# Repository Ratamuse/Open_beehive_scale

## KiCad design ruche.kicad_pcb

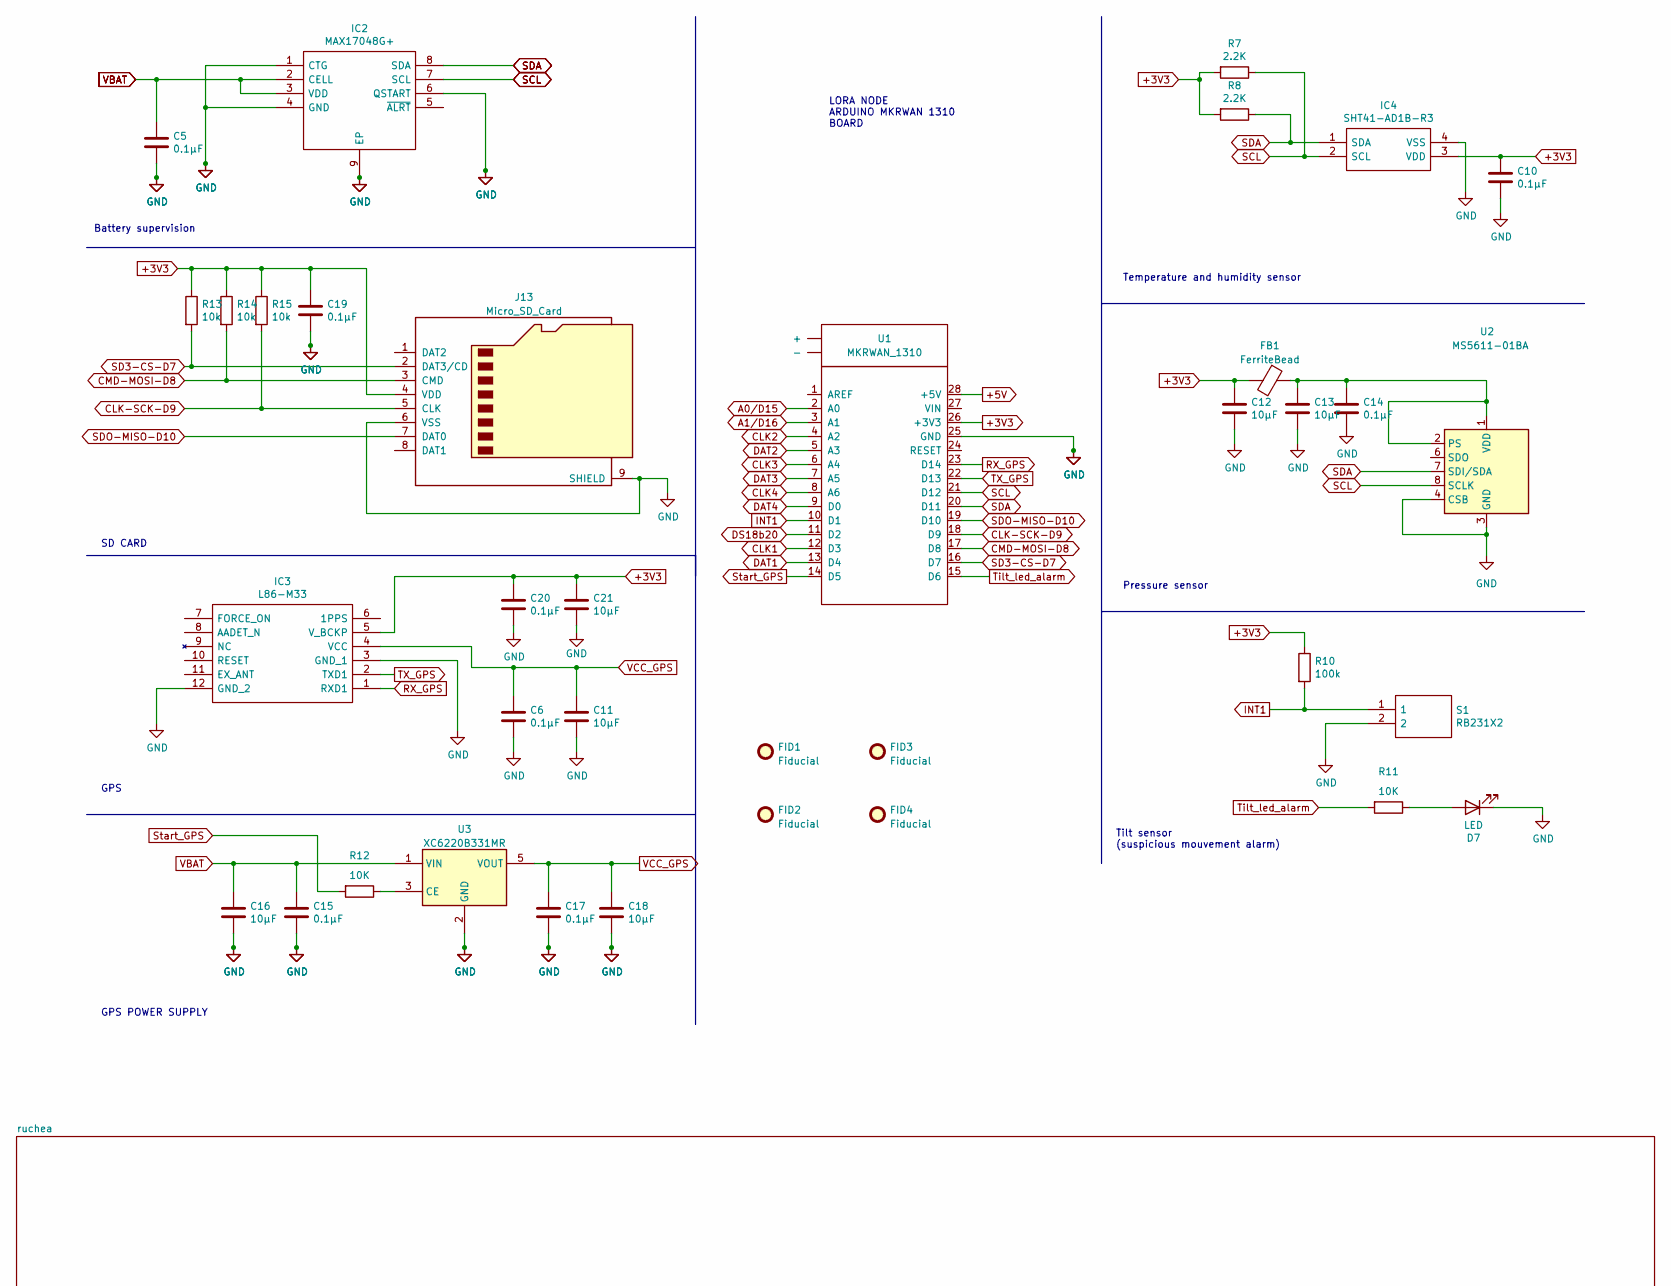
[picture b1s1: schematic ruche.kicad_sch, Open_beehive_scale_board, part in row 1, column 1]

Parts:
C5, C6, C10, C14, C17, C19, C20: 0.1µF; C_0603_1608Metric
C11, C12, C13, C18, C21: 10µF; C_0805_2012Metric
C15: 0.1µF; C_0805_2012Metric
C16: 10µF; C_0603_1608Metric
D7: LED; LED_0603_1608Metric
FB1: FerriteBead; R_0603_1608Metric
FID1, FID2, FID3, FID4: Fiducial; Fiducial_1mm_Mask3mm
IC2: MAX17048G+; SON50P200X200X80-9N-D; Manufacturer_Part_Number MAX17048G+; Mouser Part Number 700-MAX17048G+
IC3: L86-M33; L80-M39; Manufacturer_Part_Number L86-M33
IC4: SHT41-AD1B-R3; SHT41AD1BR3; Manufacturer_Part_Number SHT41-AD1B-R3; Mouser Part Number 403-SHT41-AD1B-R3
J13: Micro_SD_Card; microSD_HC_Hirose_DM3AT-SF-PEJM5
R7, R8: 2.2K; R_0603_1608Metric
R10: 100k; R_0603_1608Metric
R11, R12: 10K; R_0603_1608Metric
R13, R14, R15: 10k; R_0603_1608Metric
S1: RB231X2; Manufacturer_Part_Number RB231X2; Mouser Part Number 611-RB-231X2
U1: MKRWAN_1310; ARDUINO_ABX00012
U2: MS5611-01BA; LGA-8_3x5mm_P1.25mm
U3: XC6220B331MR; SOT-23-5

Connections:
+3V3: C10.1, C12.1, C19.1, C20.1, C21.1, FB1.2, IC3.5 (V_BCKP), IC4.3 (VDD), J13.4 (VDD), R7.2, R8.2, R10.1, R13.1, R14.1, R15.1, U1.26 (+3V3); also elsewhere on the board
+5V: U1.28 (+5V); also elsewhere on the board
A0/D15: U1.2 (A0); also elsewhere on the board
A1/D16: U1.3 (A1); also elsewhere on the board
CLK1: U1.12 (D3); also elsewhere on the board
CLK2: U1.4 (A2); also elsewhere on the board
CLK3: U1.6 (A4); also elsewhere on the board
CLK4: U1.8 (A6); also elsewhere on the board
CLK-SCK-D9: J13.5 (CLK), R15.2, U1.18 (D9)
CMD-MOSI-D8: J13.3 (CMD), R14.2, U1.17 (D8)
DAT1: U1.13 (D4); also elsewhere on the board
DAT2: U1.5 (A3); also elsewhere on the board
DAT3: U1.7 (A5); also elsewhere on the board
DAT4: U1.9 (D0); also elsewhere on the board
DS18b20: U1.11 (D2); also elsewhere on the board
GND: C5.2, C6.2, C10.2, C11.2, C12.2, C13.2, C14.2, C15.2, C16.2, C17.2, C18.2, C19.2, C20.2, C21.2, D7.1 (K), IC2.1 (CTG), IC2.4 (GND), IC2.6 (QSTART), IC2.9 (EP), IC3.3 (GND_1), IC3.12 (GND_2), IC4.4 (VSS), J13.6 (VSS), J13.9 (SHIELD), S1.2, U1.25 (GND), U2.3 (GND), U2.4 (CSB), U2.5 (CSB), U3.2 (GND); also elsewhere on the board
INT1: R10.2, S1.1, U1.10 (D1)
unnamed: C13.1, C14.1, FB1.1, U2.1 (VDD), U2.2 (PS)
unnamed: D7.2 (A), R11.1
unnamed: R12.1, U3.3 (CE)
RX_GPS: IC3.1 (RXD1), U1.23 (D14)
SCL: IC2.7 (SCL), IC4.2 (SCL), R7.1, U1.21 (D12), U2.8 (SCLK); also elsewhere on the board
SD3-CS-D7: J13.2 (DAT3/CD), R13.2, U1.16 (D7)
SDA: IC2.8 (SDA), IC4.1 (SDA), R8.1, U1.20 (D11), U2.7 (SDI/SDA); also elsewhere on the board
SDO-MISO-D10: J13.7 (DAT0), U1.19 (D10)
Start_GPS: R12.2, U1.14 (D5)
TX_GPS: IC3.2 (TXD1), U1.22 (D13)
Tilt_led_alarm: R11.2, U1.15 (D6)
VBAT: C5.1, C15.1, C16.1, IC2.2 (CELL), IC2.3 (VDD), U3.1 (VIN); also elsewhere on the board
VCC_GPS: C6.1, C11.1, C17.1, C18.1, IC3.4 (VCC), U3.5 (VOUT)

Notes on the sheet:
SD CARD
GPS
LORA NODE ARDUINO MKRWAN 1310 BOARD
Battery supervision
Tilt sensor (suspicious mouvement alarm)
Temperature and humidity sensor
Pressure sensor
GPS POWER SUPPLY

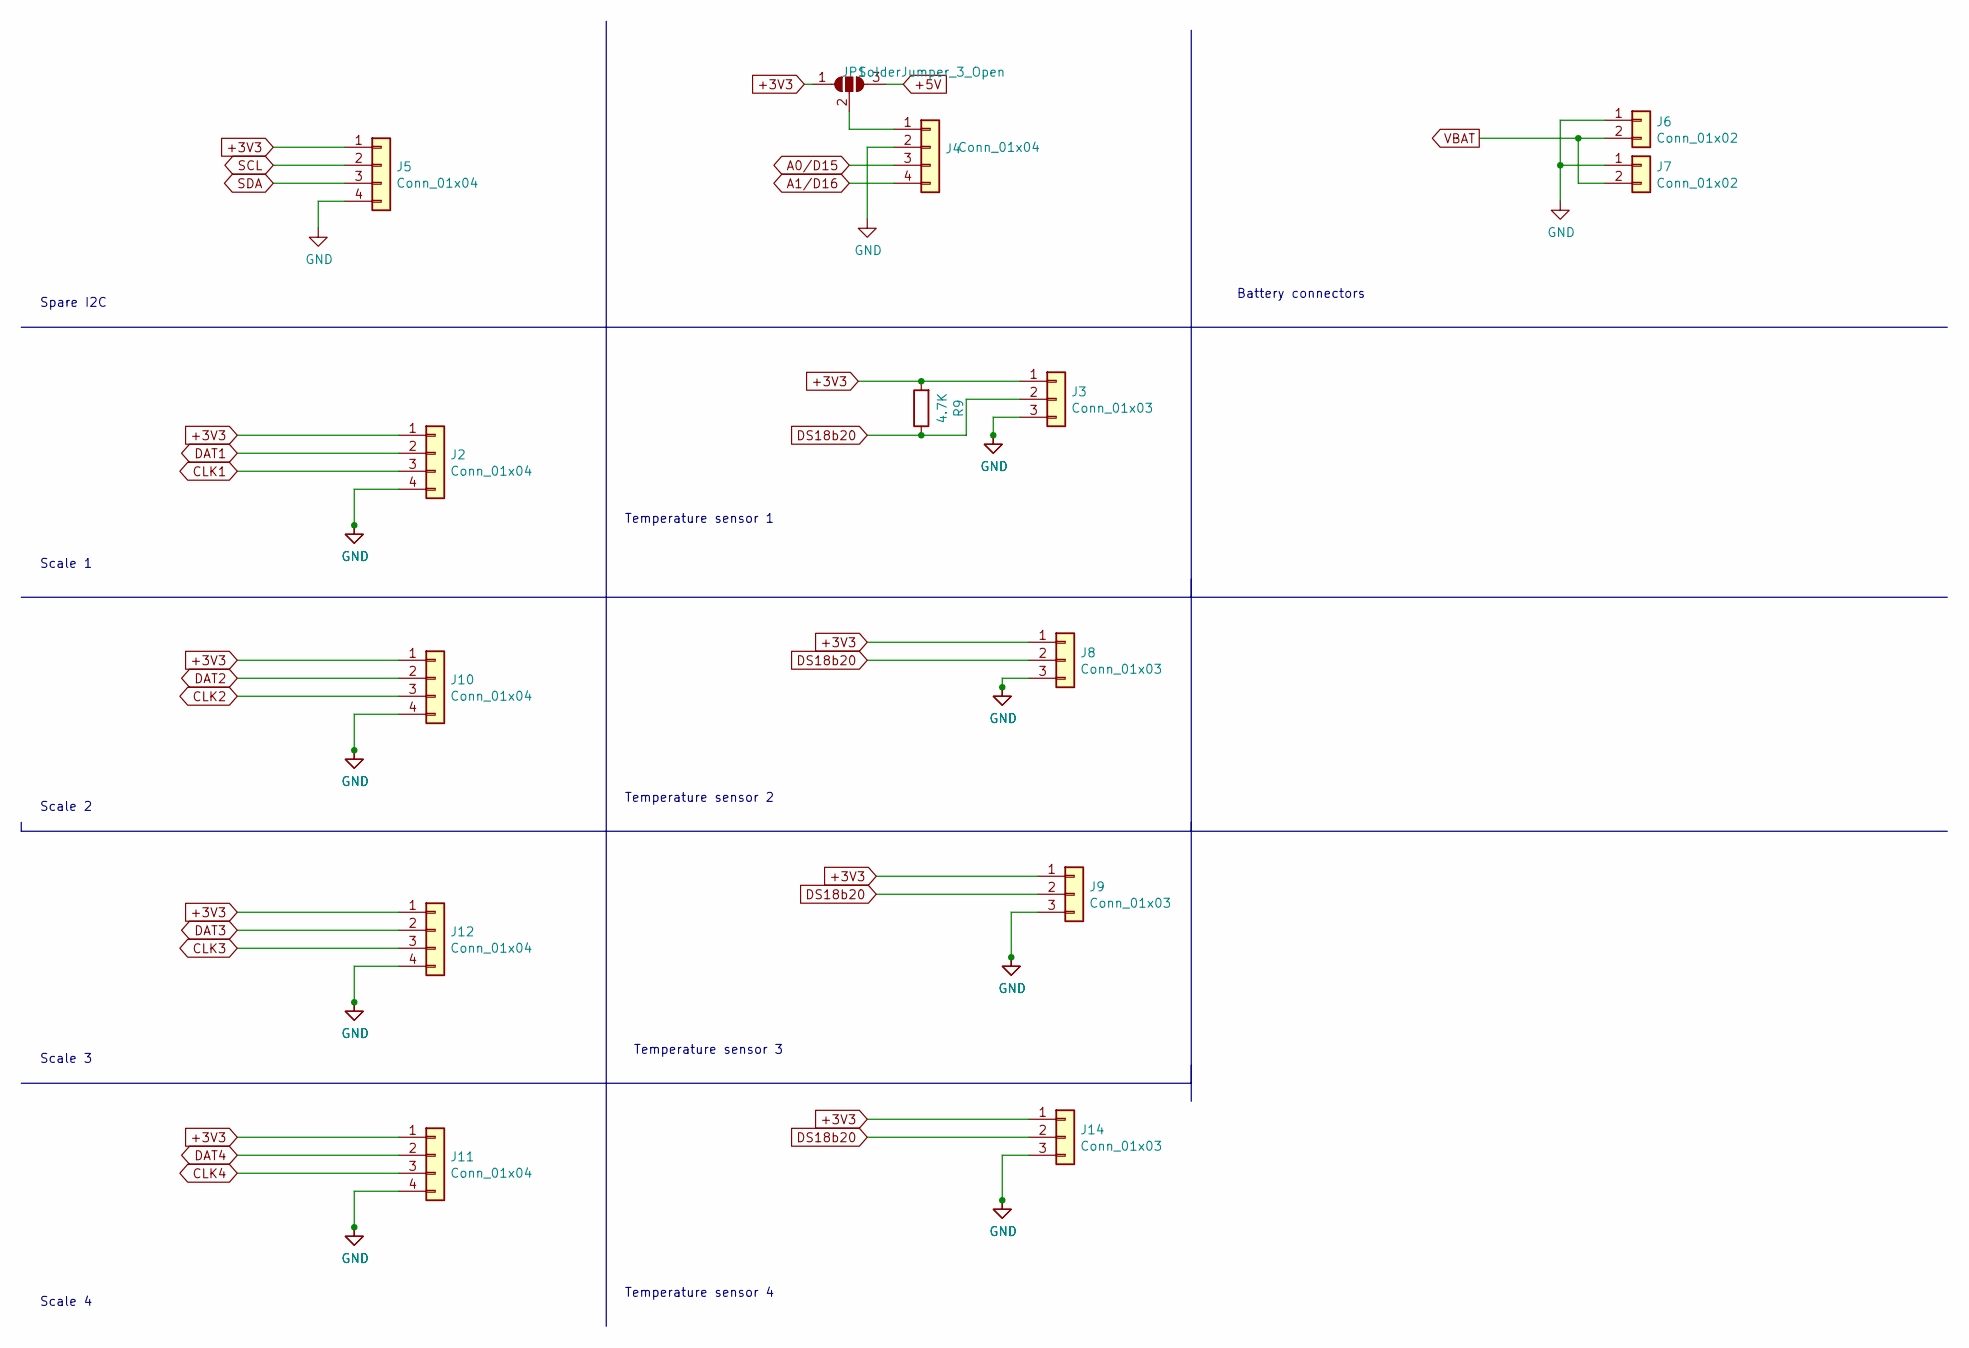
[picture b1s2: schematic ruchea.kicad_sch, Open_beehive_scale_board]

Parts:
J2, J4, J5, J10, J11, J12: Conn_01x04; JST_PH_B4B-PH-K_1x04_P2.00mm_Vertical
J3, J8, J9, J14: Conn_01x03; JST_PH_B3B-PH-K_1x03_P2.00mm_Vertical
J6, J7: Conn_01x02; JST_PH_B2B-PH-K_1x02_P2.00mm_Vertical
JP1: SolderJumper_3_Open; SolderJumper-3_P1.3mm_Open_RoundedPad1.0x1.5mm_NumberLabels
R9: 4.7K; R_0603_1608Metric

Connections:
+3V3: J2.1, J3.1, J5.1, J8.1, J9.1, J10.1, J11.1, J12.1, J14.1, JP1.1 (A), R9.2; also elsewhere on the board
+5V: JP1.3 (B); also elsewhere on the board
A0/D15: J4.3; also elsewhere on the board
A1/D16: J4.4; also elsewhere on the board
CLK1: J2.3; also elsewhere on the board
CLK2: J10.3; also elsewhere on the board
CLK3: J12.3; also elsewhere on the board
CLK4: J11.3; also elsewhere on the board
DAT1: J2.2; also elsewhere on the board
DAT2: J10.2; also elsewhere on the board
DAT3: J12.2; also elsewhere on the board
DAT4: J11.2; also elsewhere on the board
DS18b20: J3.2, J8.2, J9.2, J14.2, R9.1; also elsewhere on the board
GND: J2.4, J3.3, J4.2, J5.4, J6.1, J7.1, J8.3, J9.3, J10.4, J11.4, J12.4, J14.3; also elsewhere on the board
unnamed: J4.1, JP1.2 (C)
SCL: J5.2; also elsewhere on the board
SDA: J5.3; also elsewhere on the board
VBAT: J6.2, J7.2; also elsewhere on the board

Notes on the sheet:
Scale 4
Scale 2
Scale 3
Scale 1
Temperature sensor 2
Battery connectors
Spare I2C
Temperature sensor 1
Temperature sensor 3
Temperature sensor 4

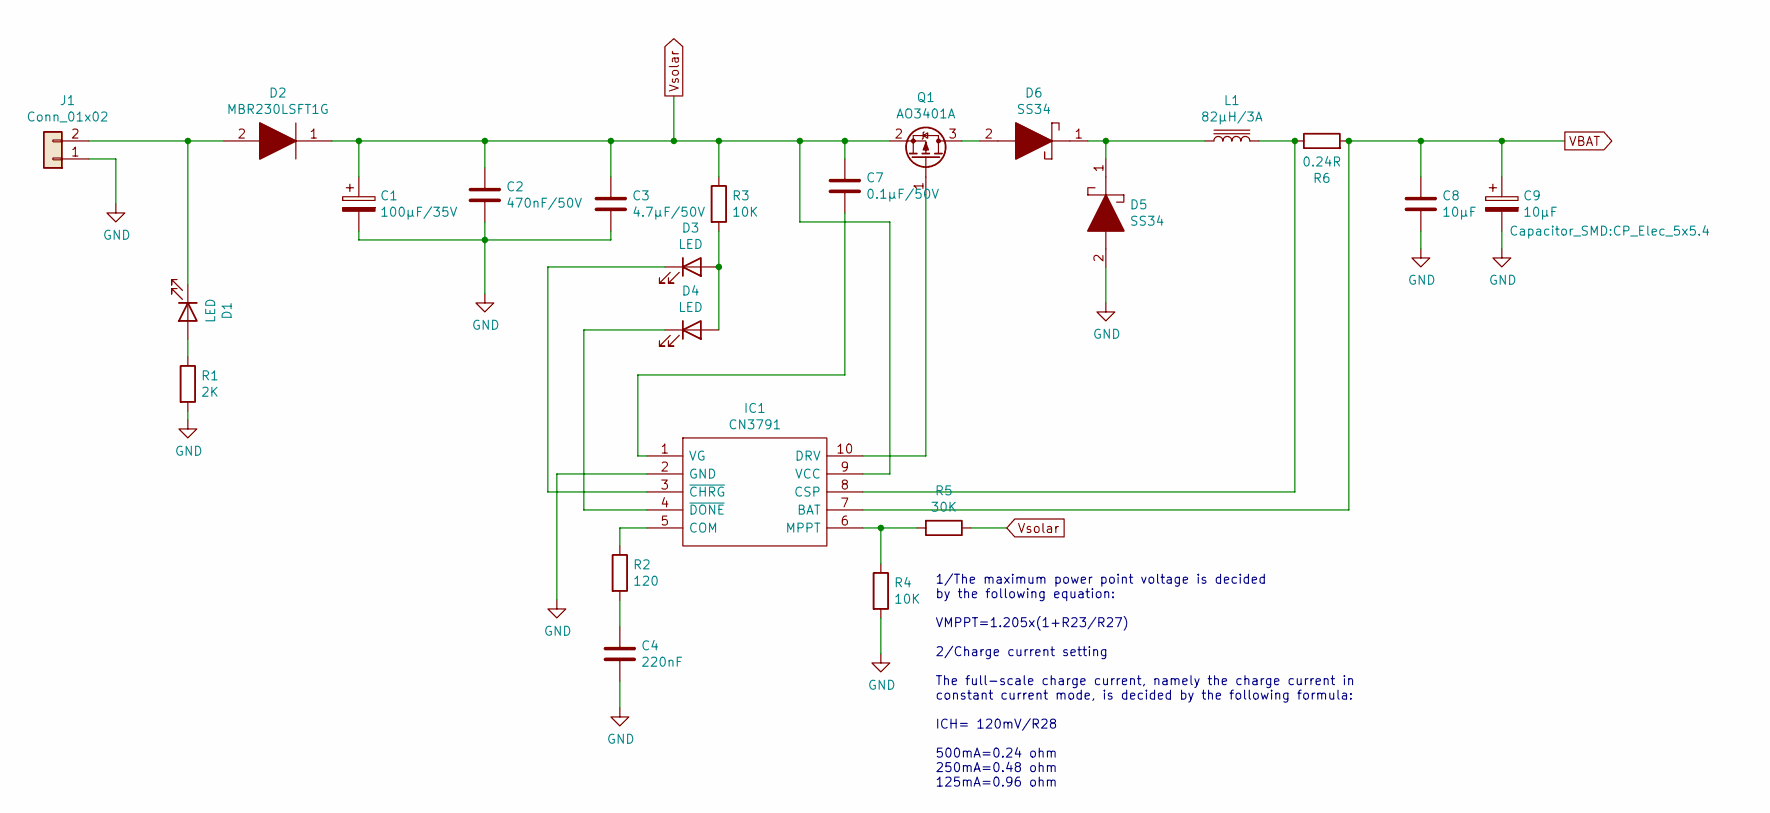
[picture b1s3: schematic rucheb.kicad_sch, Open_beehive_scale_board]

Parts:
C1: 100µF/35V; CP_Elec_6.3x7.7
C2: 470nF/50V; C_0603_1608Metric
C3: 4.7µF/50V; C_0805_2012Metric
C4: 220nF; C_0603_1608Metric
C7: 0.1µF/50V; C_0603_1608Metric
C8: 10µF; C_0805_2012Metric
C9: 10µF; CP_Elec_5x5.4
D1, D3, D4: LED; LED_0603_1608Metric_Castellated
D2: MBR230LSFT1G; SODFL3616X98N; Manufacturer_Part_Number MBR230LSFT1G; Mouser Part Number 863-MBR230LSFT1G
D5, D6: SS34; DIOM8059X256N; Manufacturer_Part_Number SS34; Mouser Part Number 512-SS34
IC1: CN3791; SOP100P600X175-10N; Manufacturer_Part_Number CN3791
J1: Conn_01x02; SHDR2W90P0X500_1X2_1060X980X1380P
L1: 82µH/3A; INDPM138126X700N
Q1: AO3401A; SOT-23
R1: 2K; R_0603_1608Metric
R2: 120; R_0603_1608Metric
R3, R4: 10K; R_0603_1608Metric
R5: 30K; R_0603_1608Metric
R6: 0.24R; R_2512_6332Metric

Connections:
GND: C1.2, C2.2, C3.2, C4.2, C8.2, C9.2, D5.2, IC1.2 (GND), J1.1, R1.2, R4.2; also elsewhere on the board
unnamed: C4.1, R2.2
unnamed: C7.2, IC1.1 (VG)
unnamed: D1.1 (K), D2.2, J1.2
unnamed: D1.2 (A), R1.1
unnamed: D3.1 (K), IC1.3 (~CHRG)
unnamed: D3.2 (A), D4.2 (A), R3.2
unnamed: D4.1 (K), IC1.4 (~DONE)
unnamed: D5.1, D6.1, L1.1
unnamed: D6.2, Q1.3 (D)
unnamed: IC1.5 (COM), R2.1
unnamed: IC1.6 (MPPT), R4.1, R5.2
unnamed: IC1.8 (CSP), L1.2, R6.1
unnamed: IC1.10 (DRV), Q1.1 (G)
VBAT: C8.1, C9.1, IC1.7 (BAT), R6.2; also elsewhere on the board
Vsolar: C1.1, C2.1, C3.1, C7.1, D2.1, IC1.9 (VCC), Q1.2 (S), R3.1, R5.1

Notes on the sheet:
1/The maximum power point voltage is decided by the following equation: VMPPT=1.205x(1+R23/R27) 2/Charge current setting The full-scale charge current, namely the charge current in constant current mode, is decided by the following formula: ICH= 120mV/R28 500mA=0.24 ohm 250mA=0.48 ohm 125mA=0.96 ohm

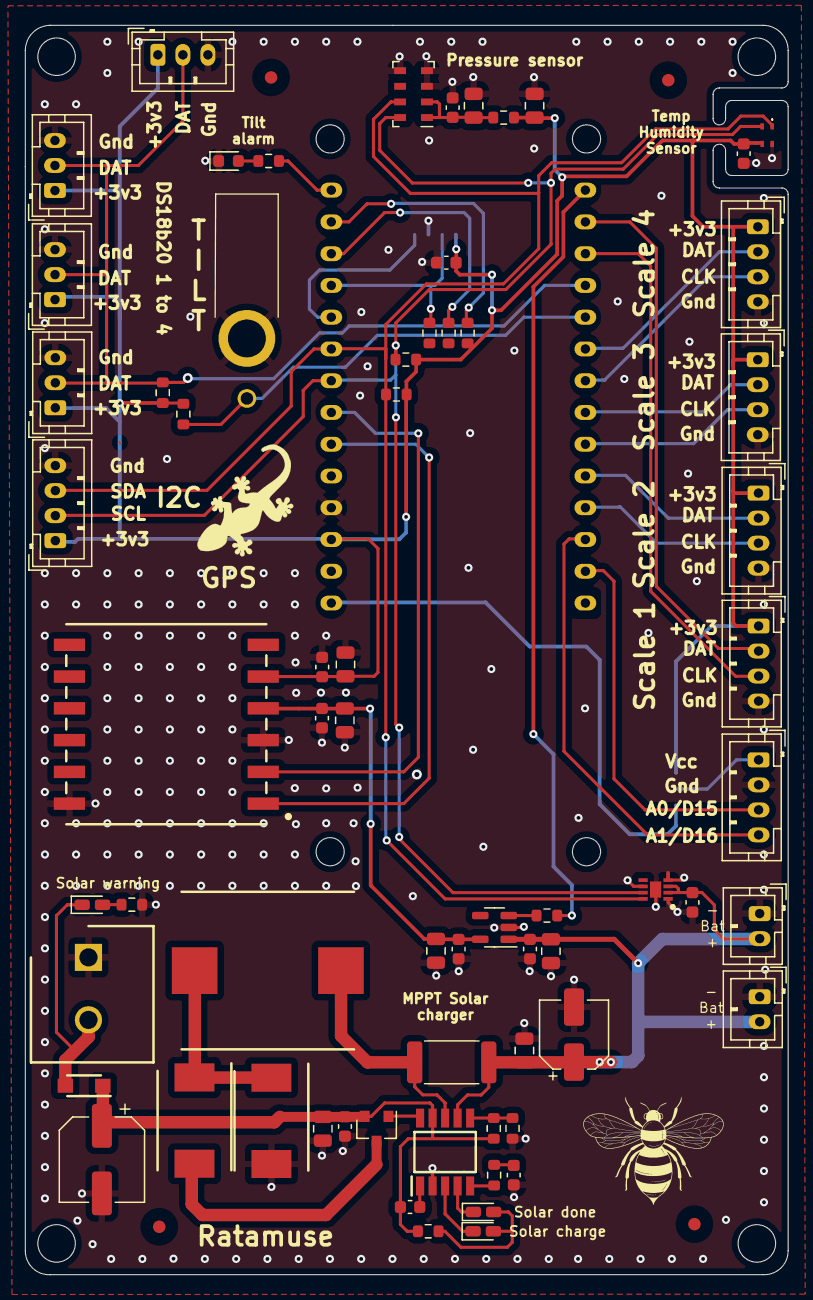
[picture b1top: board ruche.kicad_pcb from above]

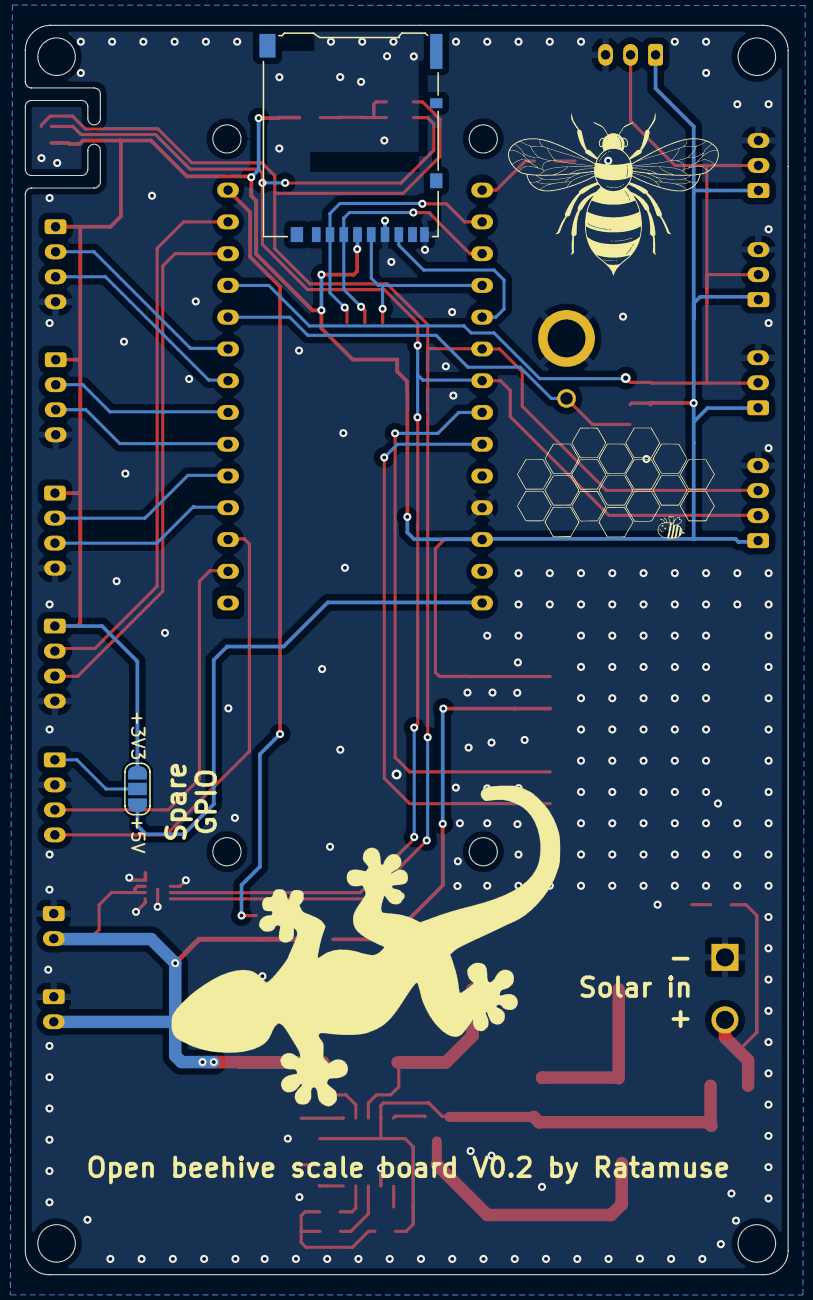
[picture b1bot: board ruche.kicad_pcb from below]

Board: 2 copper layers, 61.0 x 99.9 mm, 73 parts (2 on the bottom side), 45 nets.

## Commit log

2022-05-09 push project
2022-05-11 Correction cartouche schéma
2022-05-11 Changement des pins
2022-05-12 Modification routage
2022-05-13 Add GPS backup power supply
2022-05-13 Add graphics
2022-05-15 add temp sensor
2022-05-16 diverses modifications
2022-05-18 README
2022-05-18 Edit Readme
2022-06-05 V0.2
